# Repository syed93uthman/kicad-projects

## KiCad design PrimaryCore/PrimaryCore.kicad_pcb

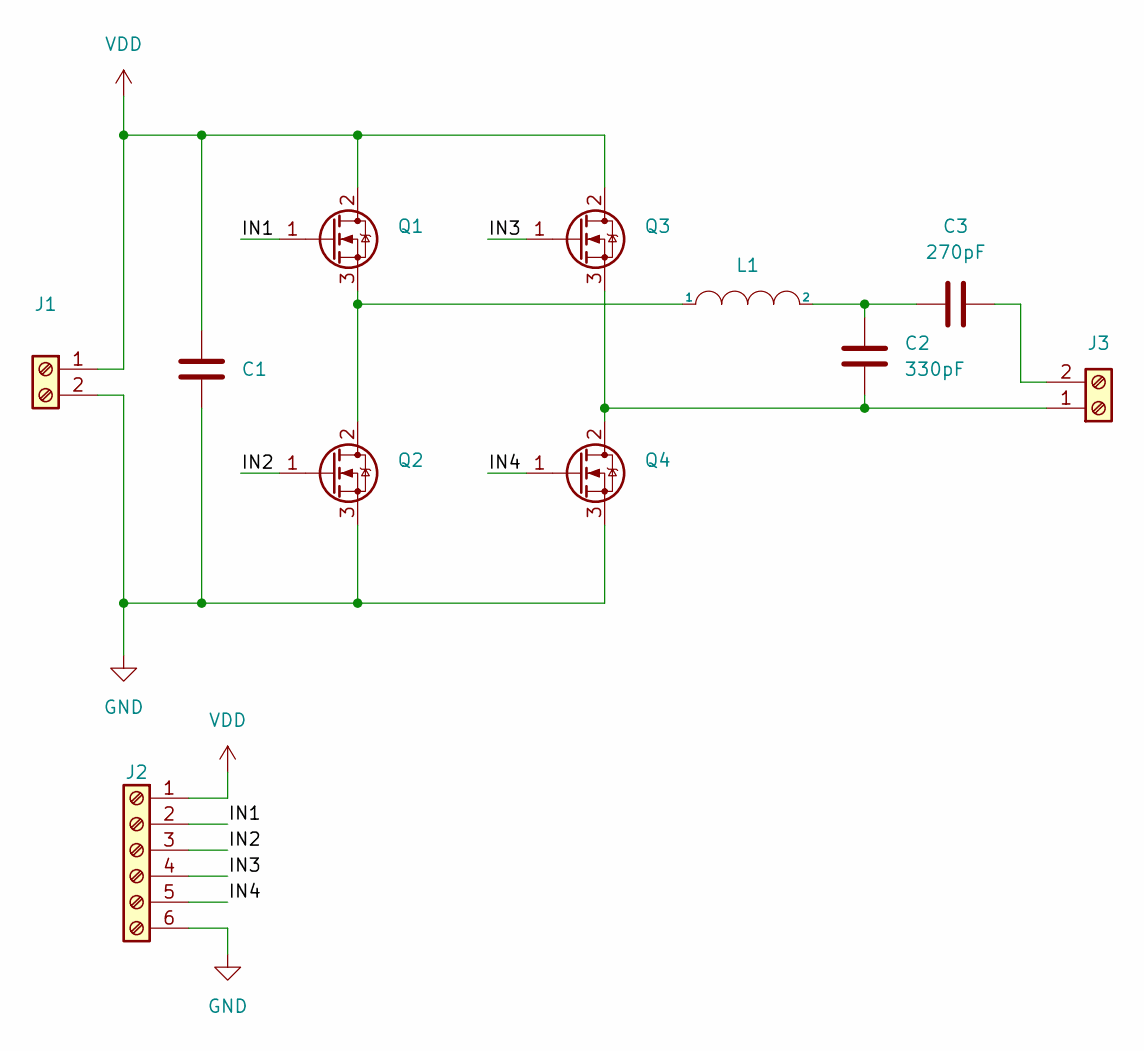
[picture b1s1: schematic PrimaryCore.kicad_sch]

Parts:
C1: C; CP_Radial_D18.0mm_P7.50mm
C2: 330pF; C_Disc_D7.5mm_W5.0mm_P10.00mm
C3: 270pF; C_Disc_D7.5mm_W5.0mm_P10.00mm
J1, J3: Screw_Terminal_01x02; TerminalBlock_Phoenix_MKDS-1,5-2-5.08_1x02_P5.08mm_Horizont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
J2: Screw_Terminal_01x06; TerminalBlock_Phoenix_PT-1,5-6-3.5-H_1x06_P3.50mm_Horizontal
L1: INDUCTOR; L_Wuerth_HCI-1890
Q1, Q2, Q3, Q4: Q_NMOS_DGS; TO-247-3_Vertical

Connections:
/IN1: J2.2, Q1.1 (G)
/IN2: J2.3, Q2.1 (G)
/IN3: J2.4, Q3.1 (G)
/IN4: J2.5, Q4.1 (G)
GND: C1.2, J1.2, J2.6, Q2.3 (S), Q4.3 (S)
unnamed: C2.1, C3.1, L1.2
unnamed: C2.2, J3.1, Q3.3 (S), Q4.2 (D)
unnamed: C3.2, J3.2
unnamed: L1.1, Q1.3 (S), Q2.2 (D)
VDD: C1.1, J1.1, J2.1, Q1.2 (D), Q3.2 (D)

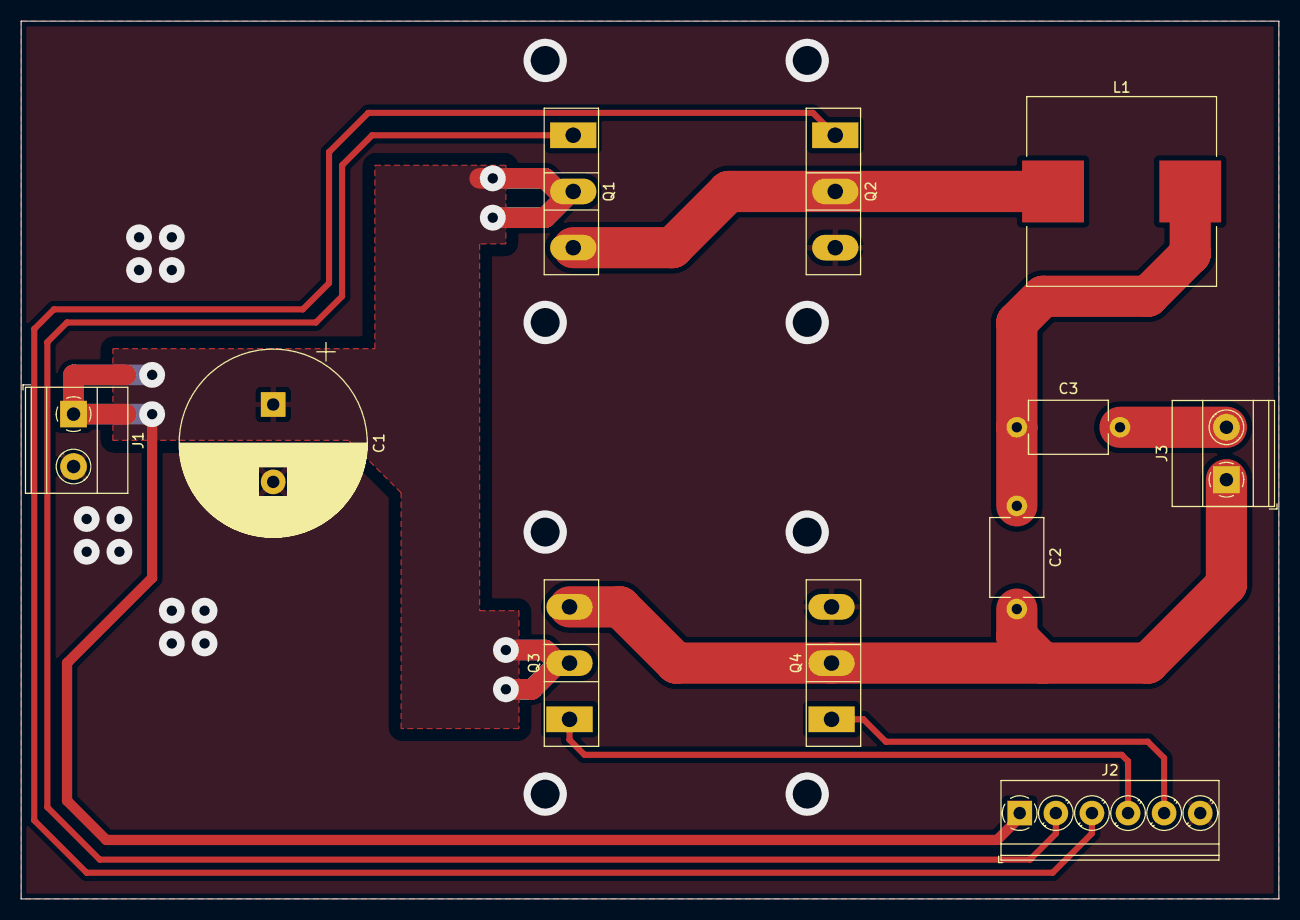
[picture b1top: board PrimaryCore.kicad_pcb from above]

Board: 2 copper layers, 121.9 x 85.1 mm, 11 parts (0 on the bottom side), 10 nets.

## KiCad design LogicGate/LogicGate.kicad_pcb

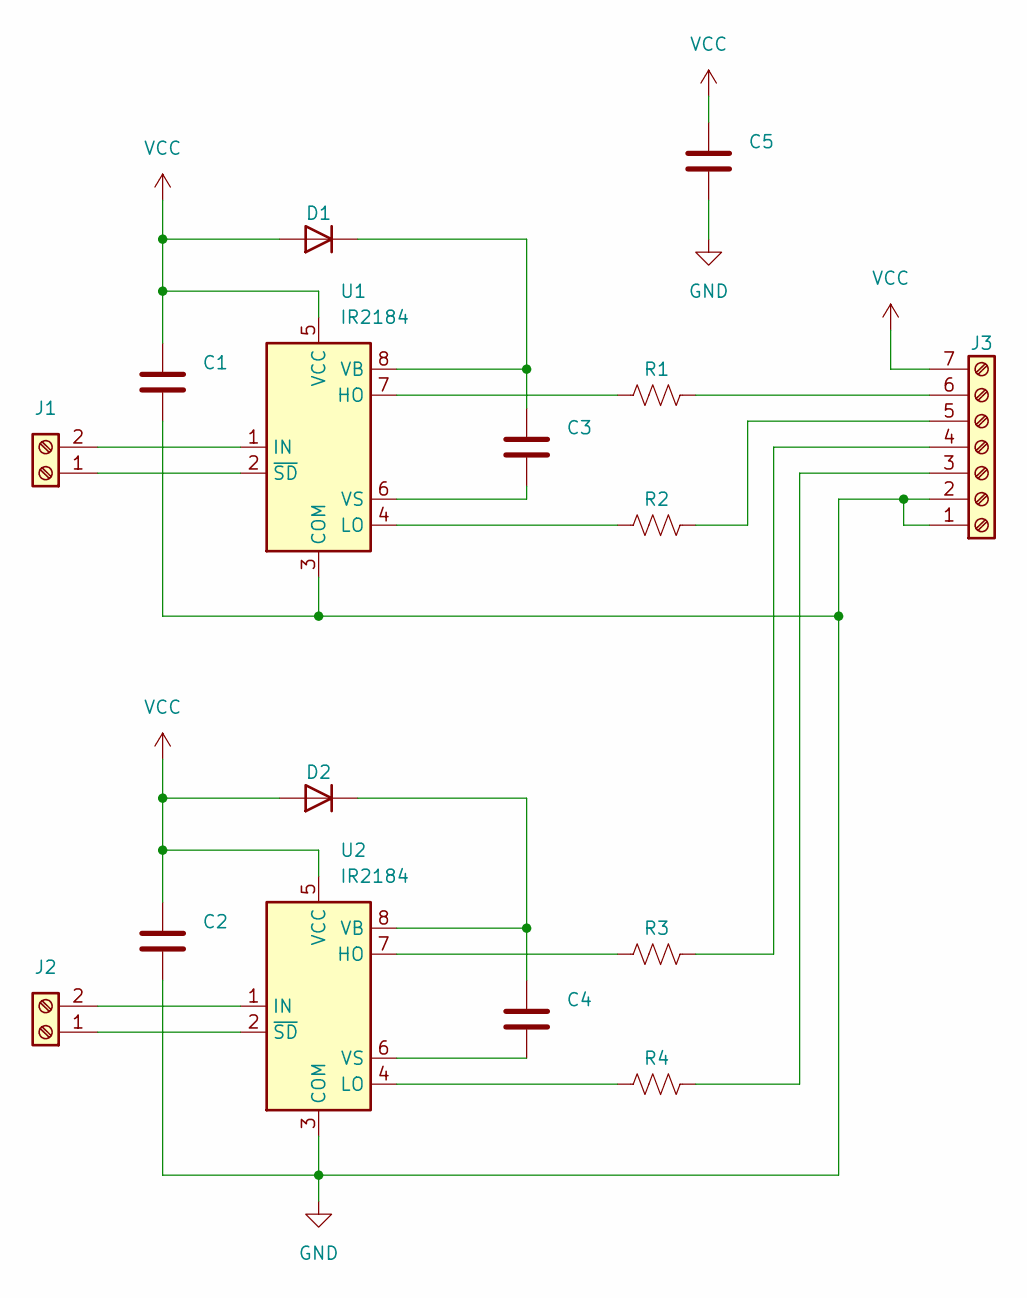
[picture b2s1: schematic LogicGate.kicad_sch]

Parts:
C1, C2, C3, C4, C5: C; C_Disc_D7.5mm_W2.5mm_P5.00mm
D1, D2: D; TO-220-2_Vertical
J1, J2: Screw_Terminal_01x02; TerminalBlock_Phoenix_MKDS-1,5-2-5.08_1x02_P5.08mm_Horizont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
J3: Screw_Terminal_01x07; TerminalBlock_Phoenix_PT-1,5-7-3.5-H_1x07_P3.50mm_Horizontal
R1, R2, R3, R4: R_US; R_Axial_DIN0207_L6.3mm_D2.5mm_P7.62mm_Horizontal
U1, U2: IR2184; DIP-8_W7.62mm_LongPads

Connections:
GND: C1.2, C2.2, C5.2, J3.1, J3.2, U1.3 (COM), U2.3 (COM)
unnamed: C3.1, D1.1 (K), U1.8 (VB)
unnamed: C3.2, U1.6 (VS)
unnamed: C4.1, D2.1 (K), U2.8 (VB)
unnamed: C4.2, U2.6 (VS)
unnamed: J1.1, U1.2 (~SD)
unnamed: J1.2, U1.1 (IN)
unnamed: J2.1, U2.2 (~SD)
unnamed: J2.2, U2.1 (IN)
unnamed: J3.3, R4.1
unnamed: J3.4, R3.1
unnamed: J3.5, R2.1
unnamed: J3.6, R1.1
unnamed: R1.2, U1.7 (HO)
unnamed: R2.2, U1.4 (LO)
unnamed: R3.2, U2.7 (HO)
unnamed: R4.2, U2.4 (LO)
VCC: C1.1, C2.1, C5.1, D1.2 (A), D2.2 (A), J3.7, U1.5 (VCC), U2.5 (VCC)

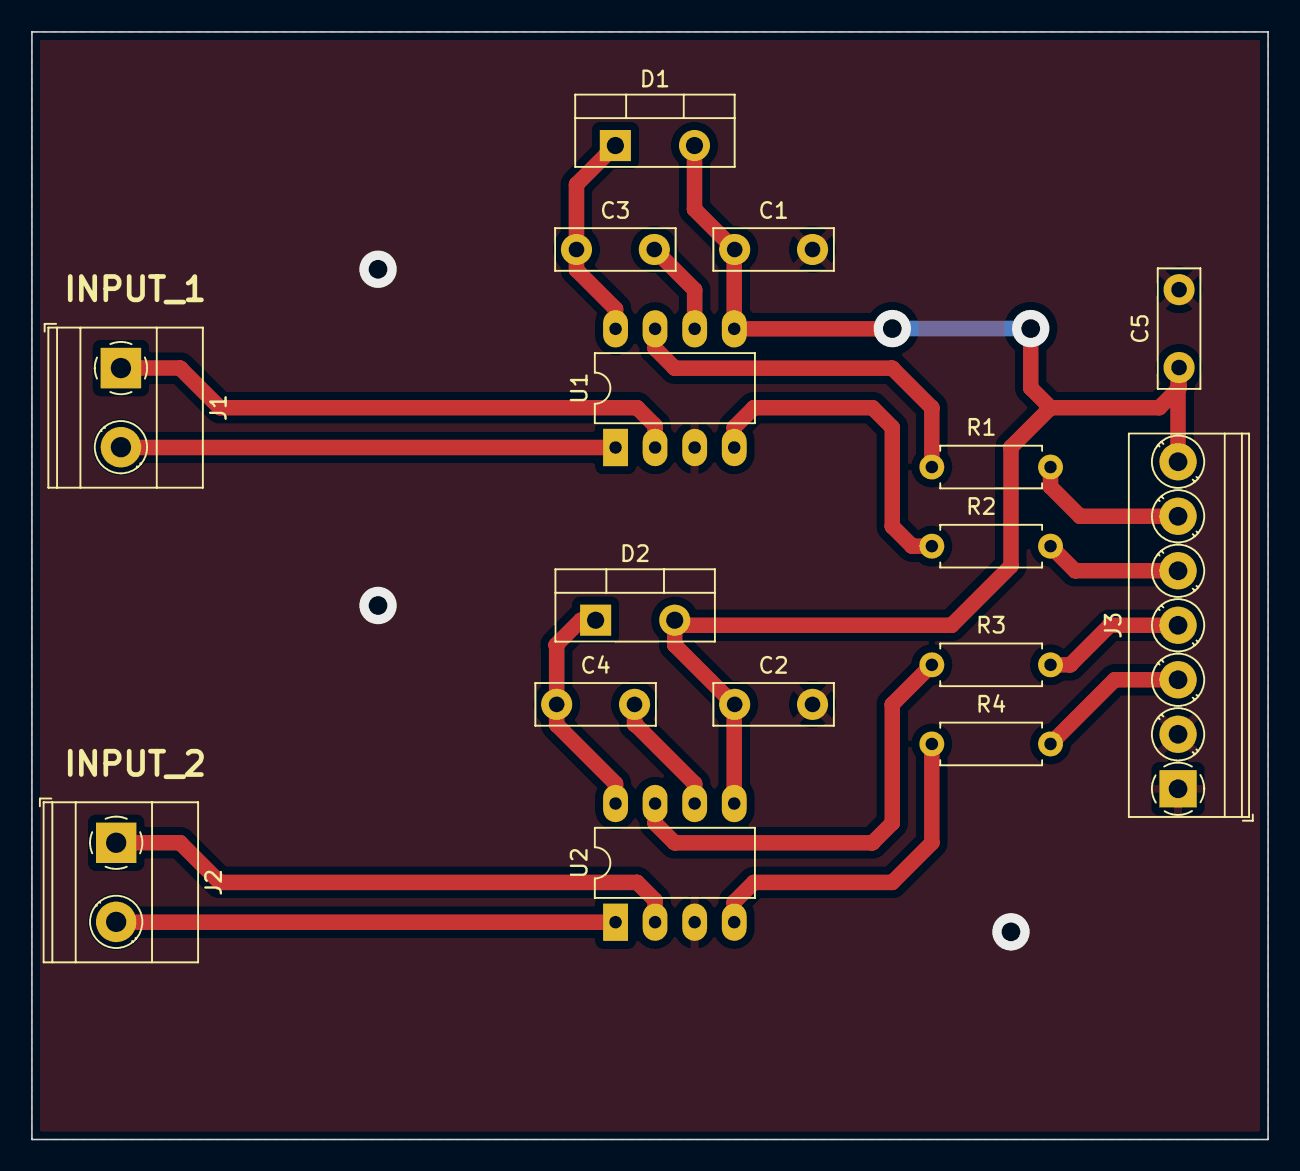
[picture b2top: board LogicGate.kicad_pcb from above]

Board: 2 copper layers, 79.4 x 71.1 mm, 16 parts (0 on the bottom side), 18 nets.

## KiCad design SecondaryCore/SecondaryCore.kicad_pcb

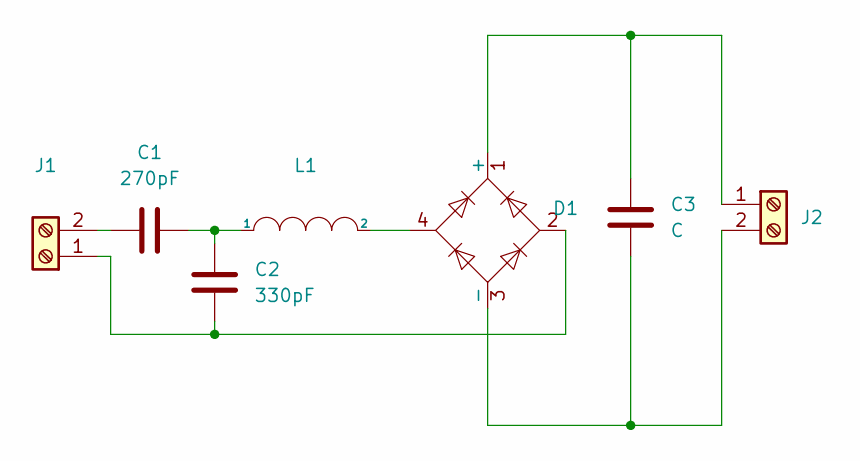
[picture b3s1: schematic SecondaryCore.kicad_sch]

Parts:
C1: 270pF; C_Disc_D7.5mm_W5.0mm_P10.00mm
C2: 330pF; C_Disc_D7.5mm_W5.0mm_P10.00mm
C3: C; CP_Radial_D18.0mm_P7.50mm
D1: VS-KBPC804; Diode_Bridge_Vishay_KBPC6
J1, J2: Screw_Terminal_01x02; TerminalBlock_Phoenix_MKDS-1,5-2-5.08_1x02_P5.08mm_Horizont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
L1: INDUCTOR; L_Wuerth_HCI-1890

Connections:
unnamed: C1.1, J1.2
unnamed: C1.2, C2.1, L1.1
unnamed: C2.2, D1.2, J1.1
unnamed: C3.1, D1.3 (-), J2.2
unnamed: C3.2, D1.1 (+), J2.1
unnamed: D1.4, L1.2

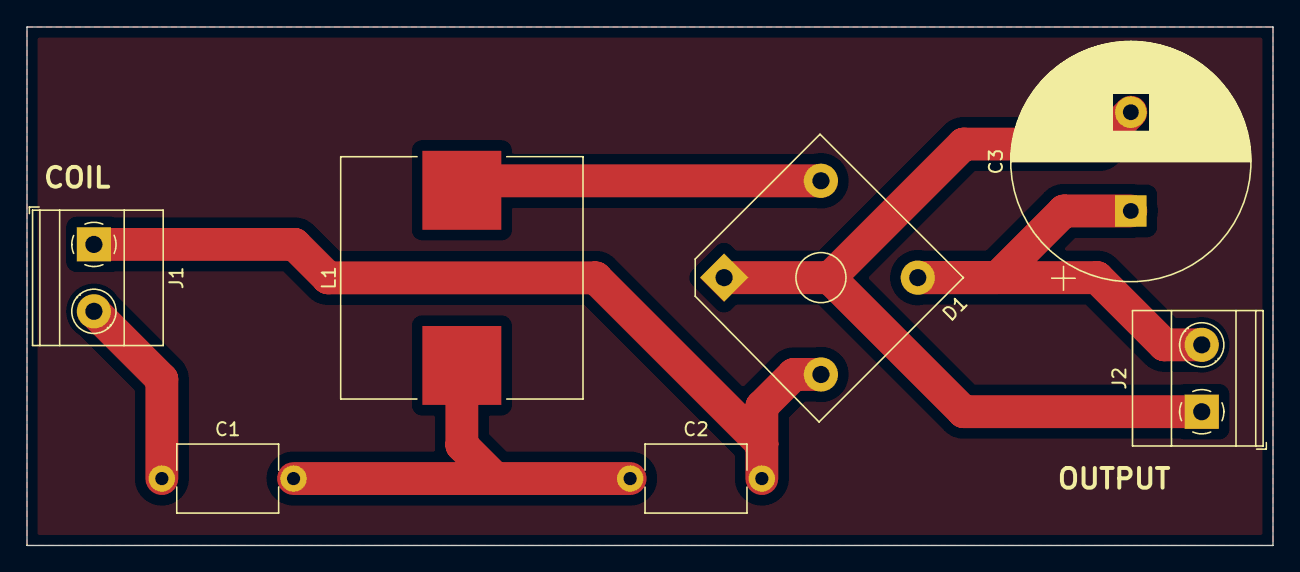
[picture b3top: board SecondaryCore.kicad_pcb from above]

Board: 2 copper layers, 94.6 x 39.4 mm, 7 parts (0 on the bottom side), 6 nets.

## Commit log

2023-03-02 Add gitignore kicad6
2023-03-02 update LogicGate project
2023-03-06 Change Cap footpackage p 10mm
2023-03-06 update gitignore cache
2023-03-06 latest route pcb
2023-03-06 redo changes on gitignore
